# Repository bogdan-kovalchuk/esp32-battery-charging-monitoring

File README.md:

# ESP32 Battery Charging Monitor

An ESP32-based 12 V battery voltage monitor. The firmware measures battery
voltage, while a Flask backend delivers notifications to a Signal group through
`signal-cli`.

```text
ESP32 -- HTTP or HTTPS --> Flask -- SQLite outbox --> signal-cli --> Signal group
```

## Features

- Voltage sampling every 60 seconds
- Immediate `ALERT` when voltage drops to or below the critical threshold
- Immediate `INFO` when voltage recovers
- Separate reminder intervals for INFO and ALERT states
- Fallback WiFi access point with a web configuration form
- CRC-protected ESP32 configuration stored in alternating NVS slots
- Persistent SQLite outbox with retries and `event_id` deduplication
- Optional HTTP or HTTPS transport
- Health check and Prometheus metrics

## Project structure

| Path | Purpose |
|---|---|
| `firmware/` | PlatformIO/Arduino firmware for ESP32 |
| `server/` | Flask API and signal-cli integration |
| `firmware/test/` | Host-side firmware logic tests |
| `server/tests/` | Backend tests |
| `hardware/battery-monitor-rev-a/` | KiCad 10 project of the rev-a PCB and its production package |

## Hardware

### Rev-a PCB

[`hardware/battery-monitor-rev-a/`](hardware/battery-monitor-rev-a/) is a
dedicated board: ESP32-S3-WROOM-1-N16R8, Ra-02 433 MHz LoRa, ADS1115 battery
voltage measurement for 6-24 V systems (48 V by a part swap), switched LED
voltmeter output; 4 layers, 62 x 50 mm, hand assembly.

| Path | Content |
|---|---|
| `hardware/battery-monitor-rev-a/*.kicad_*`, `lib/`, `3dmodels/` | KiCad 10 schematic (5 sheets), board, design rules, project library and 3D models |
| [`production/`](hardware/battery-monitor-rev-a/production/README.md) | Gerber ZIP for a standard JLCPCB 4-layer order, drill, IPC-D-356, BOM, purchase workbook, schematic PDF, assembly drawings, STEP, `manifest.sha256` |
| [`ASSEMBLY-NOTES.md`](hardware/battery-monitor-rev-a/production/03-documentation/ASSEMBLY-NOTES.md) | Pin map, hand-assembly order, firmware obligations, bring-up tests |

The firmware in `firmware/` still targets the ESP32 DevKit prototype below; it
is not yet ported to the ESP32-S3 and the rev-a pin map.

### DevKit prototype

| Signal | ESP32 pin | Notes |
|---|---:|---|
| Voltage divider | GPIO 32 | ADC input, 30 kOhm / 7.5 kOhm |
| Button | GPIO 34 | Requires an external 10 kOhm pull-down |
| Divider/gauge enable | GPIO 4 | Through a transistor and 1 kOhm resistor |

The ADC calibration factor is `CORR_FACTOR` in
`firmware/include/app_config.h`.

## Firmware

Create the configuration file:

```bash
cp firmware/include/secrets.h.example firmware/include/secrets.h
```

Set the WiFi credentials, backend host, API token, and passwords. `secrets.h`
is ignored by Git. Its values provide the initial defaults; after the first
boot, runtime configuration is stored in NVS.

Build and upload:

```bash
pio run -d firmware -e esp32dev
pio run -d firmware -e esp32dev -t upload
pio device monitor -b 115200
```

### HTTP and HTTPS

The configuration template uses HTTP by default:

```cpp
#define SERVER_PORT 5000
#define SERVER_USE_TLS 0
#define SERVER_ROOT_CA ""
```

Existing private `secrets.h` files without the TLS macros also continue to use
HTTP.

To enable HTTPS, select the TLS port and provide the PEM CA root:

```cpp
#define SERVER_PORT 443
#define SERVER_USE_TLS 1
#define SERVER_ROOT_CA \
  "-----BEGIN CERTIFICATE-----\n" \
  "...\n" \
  "-----END CERTIFICATE-----\n"
```

The CA root is required only when HTTPS is enabled.

### Fallback access point

If the ESP32 cannot connect to WiFi within 30 seconds, it starts the configured
fallback access point while continuing STA connection attempts in the
background.

1. Connect to the network configured by `AP_SSID`.
2. Open `http://192.168.4.1/`.
3. Sign in with `WEB_USER` and `WEB_PASSWORD`.
4. Update the WiFi, backend, threshold, and interval settings.
5. Save the configuration.

The fallback access point stops after the STA connection remains stable.
Holding the button for 10 seconds restores the compile-time defaults.

## Backend

The backend requires Python 3.10+ and an installed `signal-cli`. Follow the
official [signal-cli README](https://github.com/AsamK/signal-cli) for current
installation and account setup instructions.

```bash
cd server
python3 -m venv .venv
. .venv/bin/activate
pip install -r requirements.txt
cp .env.example .env
```

Set at least these values:

```dotenv
SIGNAL_USER=+380XXXXXXXXX
SIGNAL_GROUP_ID=group-id
API_TOKEN=same-token-as-in-firmware
```

Start the backend:

```bash
python -m battery_monitor.wsgi
```

Before opening the socket, the backend verifies the signal-cli binary, account,
and target group. Accepted events are persisted in
`server/.data/outbox.sqlite3` and then sent sequentially through signal-cli.

## API

`POST /send` requires `Authorization: Bearer <API_TOKEN>`.

```json
{
  "event_id": "device-boot-sequence",
  "device_id": "BATT#1",
  "msg_type": "ALERT",
  "voltage": 10.8,
  "critical_voltage": 11.0
}
```

| Status | Meaning |
|---:|---|
| `202` | Event persisted or previously accepted |
| `400` | Invalid payload |
| `401` | Invalid API token |
| `413` | Request body too large |
| `503` | Outbox full; retry with the same `event_id` |

Additional endpoints:

- `GET /healthcheck` – public unless `HEALTHCHECK_REQUIRE_AUTH=true`
- `GET /metrics` – requires the bearer token unless `METRICS_REQUIRE_AUTH=false`
- `GET /signal-cli/version` – follows the `/metrics` setting

## Tests

```bash
pio test -d firmware -e native
pio run -d firmware -e esp32dev-ci

cd server
python -m pytest
```

On Windows, `firmware/scripts/native_toolchain.py` lets `pio test -e native`
use the MinGW toolchain bundled with PlatformIO when no `gcc` is on `PATH`.

`esp32dev-ci` uses dummy credentials for compile checks only. Upload firmware
with the `esp32dev` environment and your own `secrets.h`.

## Limitations

- HTTP does not encrypt the API token; enable HTTPS on untrusted networks.
- The ESP32 configuration portal uses HTTP.
- ESP32 NVS is not encrypted.
- Devices using the same `API_TOKEN` share access. Use individual tokens when
  separate device identities are required.

## License

[MIT](LICENSE)

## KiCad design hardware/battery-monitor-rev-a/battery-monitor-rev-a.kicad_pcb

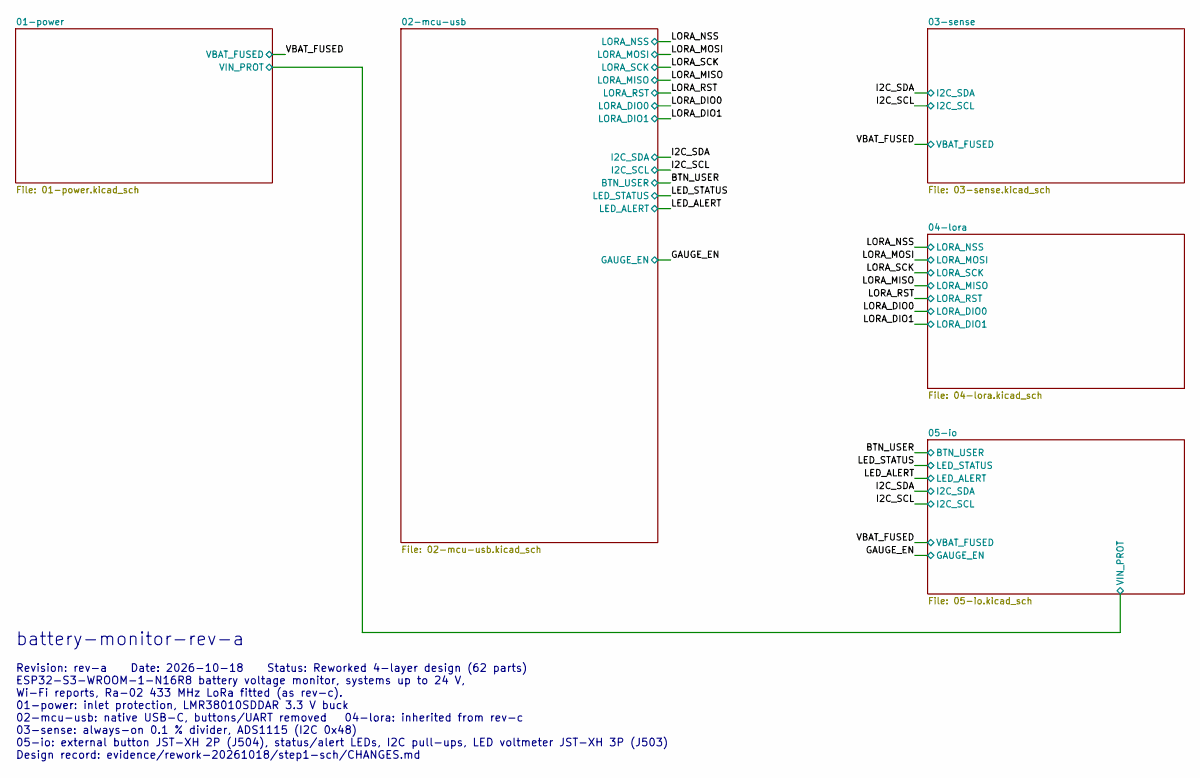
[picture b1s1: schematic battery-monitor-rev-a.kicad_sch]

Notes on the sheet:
battery-monitor-rev-a
Revision: rev-a Date: 2026-10-18 Status: Reworked 4-layer design (62 parts) ESP32-S3-WROOM-1-N16R8 battery voltage monitor, systems up to 24 V, Wi-Fi reports, Ra-02 433 MHz LoRa fitted (as rev-c). 01-power: inlet protection, LMR38010SDDAR 3.3 V buck 02-mcu-usb: native USB-C, buttons/UART removed 04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

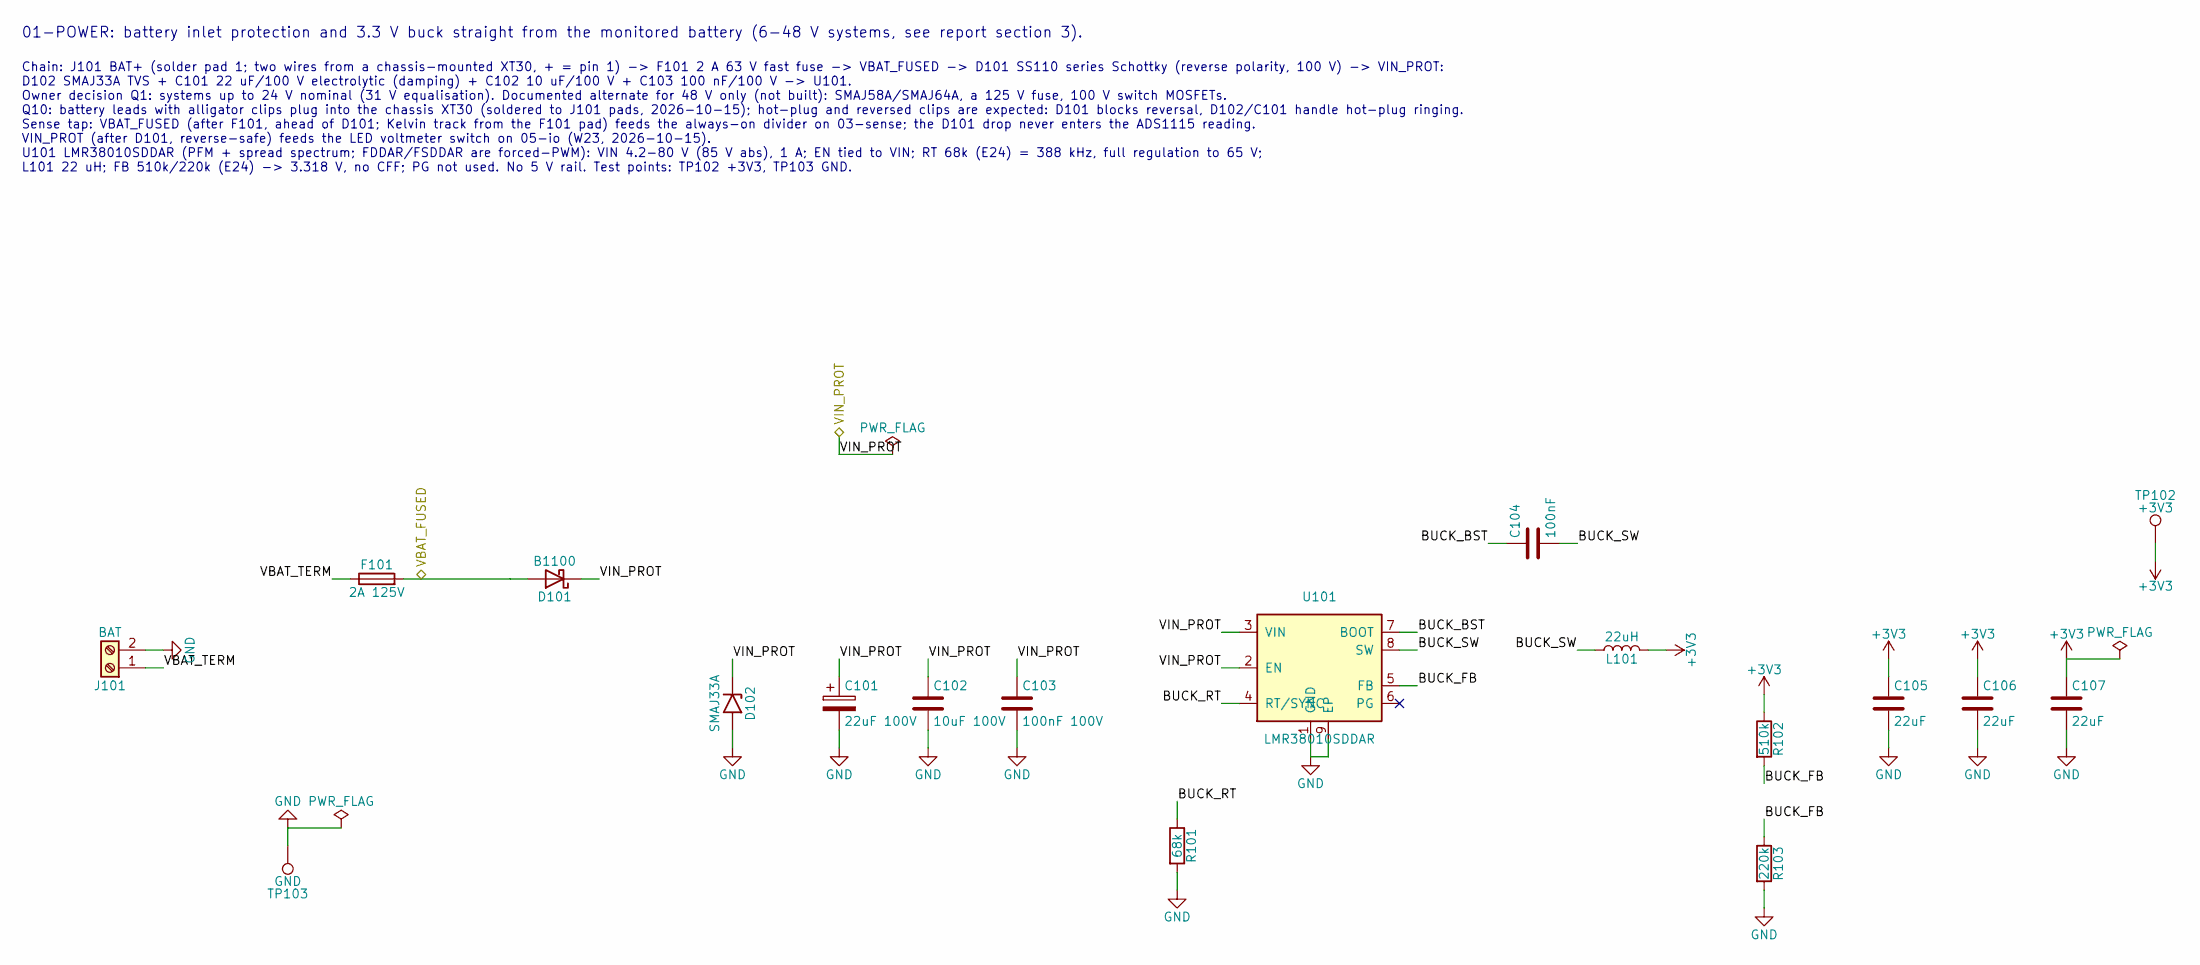
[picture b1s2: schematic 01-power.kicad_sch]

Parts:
C101: 22uF 100V; CP_Elec_8x10; MPN EEE-FK2A220P
C102: 10uF 100V; C_1210_3225Metric; MPN GRM32EC72A106KE05L
C103: 100nF 100V; C_0603_1608Metric; MPN CL10B104KC8NNNC
C104: 100nF; C_0603_1608Metric; MPN CL10B104KB8NNNC
C105, C106, C107: 22uF; C_0805_2012Metric; MPN GRM21BR61E226ME44L
D101: B1100; D_SMA; MPN B1100-13-F
D102: SMAJ33A; D_SMA; MPN SMAJ33A-TR
F101: 2A 125V; Fuse_Littelfuse-NANO2-451_453; MPN 0451002.MRL
J101: BAT; SolderWire-0.75sqmm_1x02_P4.8mm_D1.25mm_OD2.3mm
L101: 22uH; L_Bourns_SRN6045TA; MPN SRN6045-220M
R101: 68k; R_0603_1608Metric; MPN RC0603FR-0768KL
R102: 510k; R_0603_1608Metric; MPN 0603SAF5103T5E
R103: 220k; R_0603_1608Metric; MPN RC0603FR-07220KL
TP102: +3V3; TestPoint_Pad_D1.5mm
TP103: GND; TestPoint_Pad_D1.5mm
U101: LMR38010SDDAR; TI_SO-PowerPAD-8; MPN LMR38010SDDAR

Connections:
+3V3: C105.1, C106.1, C107.1, L101.2, R102.1, TP102.1; also elsewhere on the board
/01-power/BUCK_BST: C104.1, U101.7 (BOOT)
/01-power/BUCK_FB: R102.2, R103.1, U101.5 (FB)
/01-power/BUCK_RT: R101.1, U101.4 (RT/SYNC)
/01-power/BUCK_SW: C104.2, L101.1, U101.8 (SW)
/01-power/VBAT_TERM: F101.1, J101.1
/01-power/VIN_PROT: C101.1, C102.1, C103.1, D101.1 (K), D102.1 (A1), U101.2 (EN), U101.3 (VIN); also elsewhere on the board
/VBAT_FUSED: D101.2 (A), F101.2; also elsewhere on the board
GND: C101.2, C102.2, C103.2, C105.2, C106.2, C107.2, D102.2 (A2), J101.2, R101.2, R103.2, TP103.1, U101.1 (GND), U101.9 (EP); also elsewhere on the board

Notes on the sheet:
01-POWER: battery inlet protection and 3.3 V buck straight from the monitored battery (6-48 V systems, see report section 3).
Chain: J101 BAT+ (solder pad 1; two wires from a chassis-mounted XT30, + = pin 1) -> F101 2 A 63 V fast fuse -> VBAT_FUSED -> D101 SS110 series Schottky (reverse polarity, 100 V) -> VIN_PROT: D102 SMAJ33A TVS + C101 22 uF/100 V electrolytic (damping) + C102 10 uF/100 V + C103 100 nF/100 V -> U101. 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

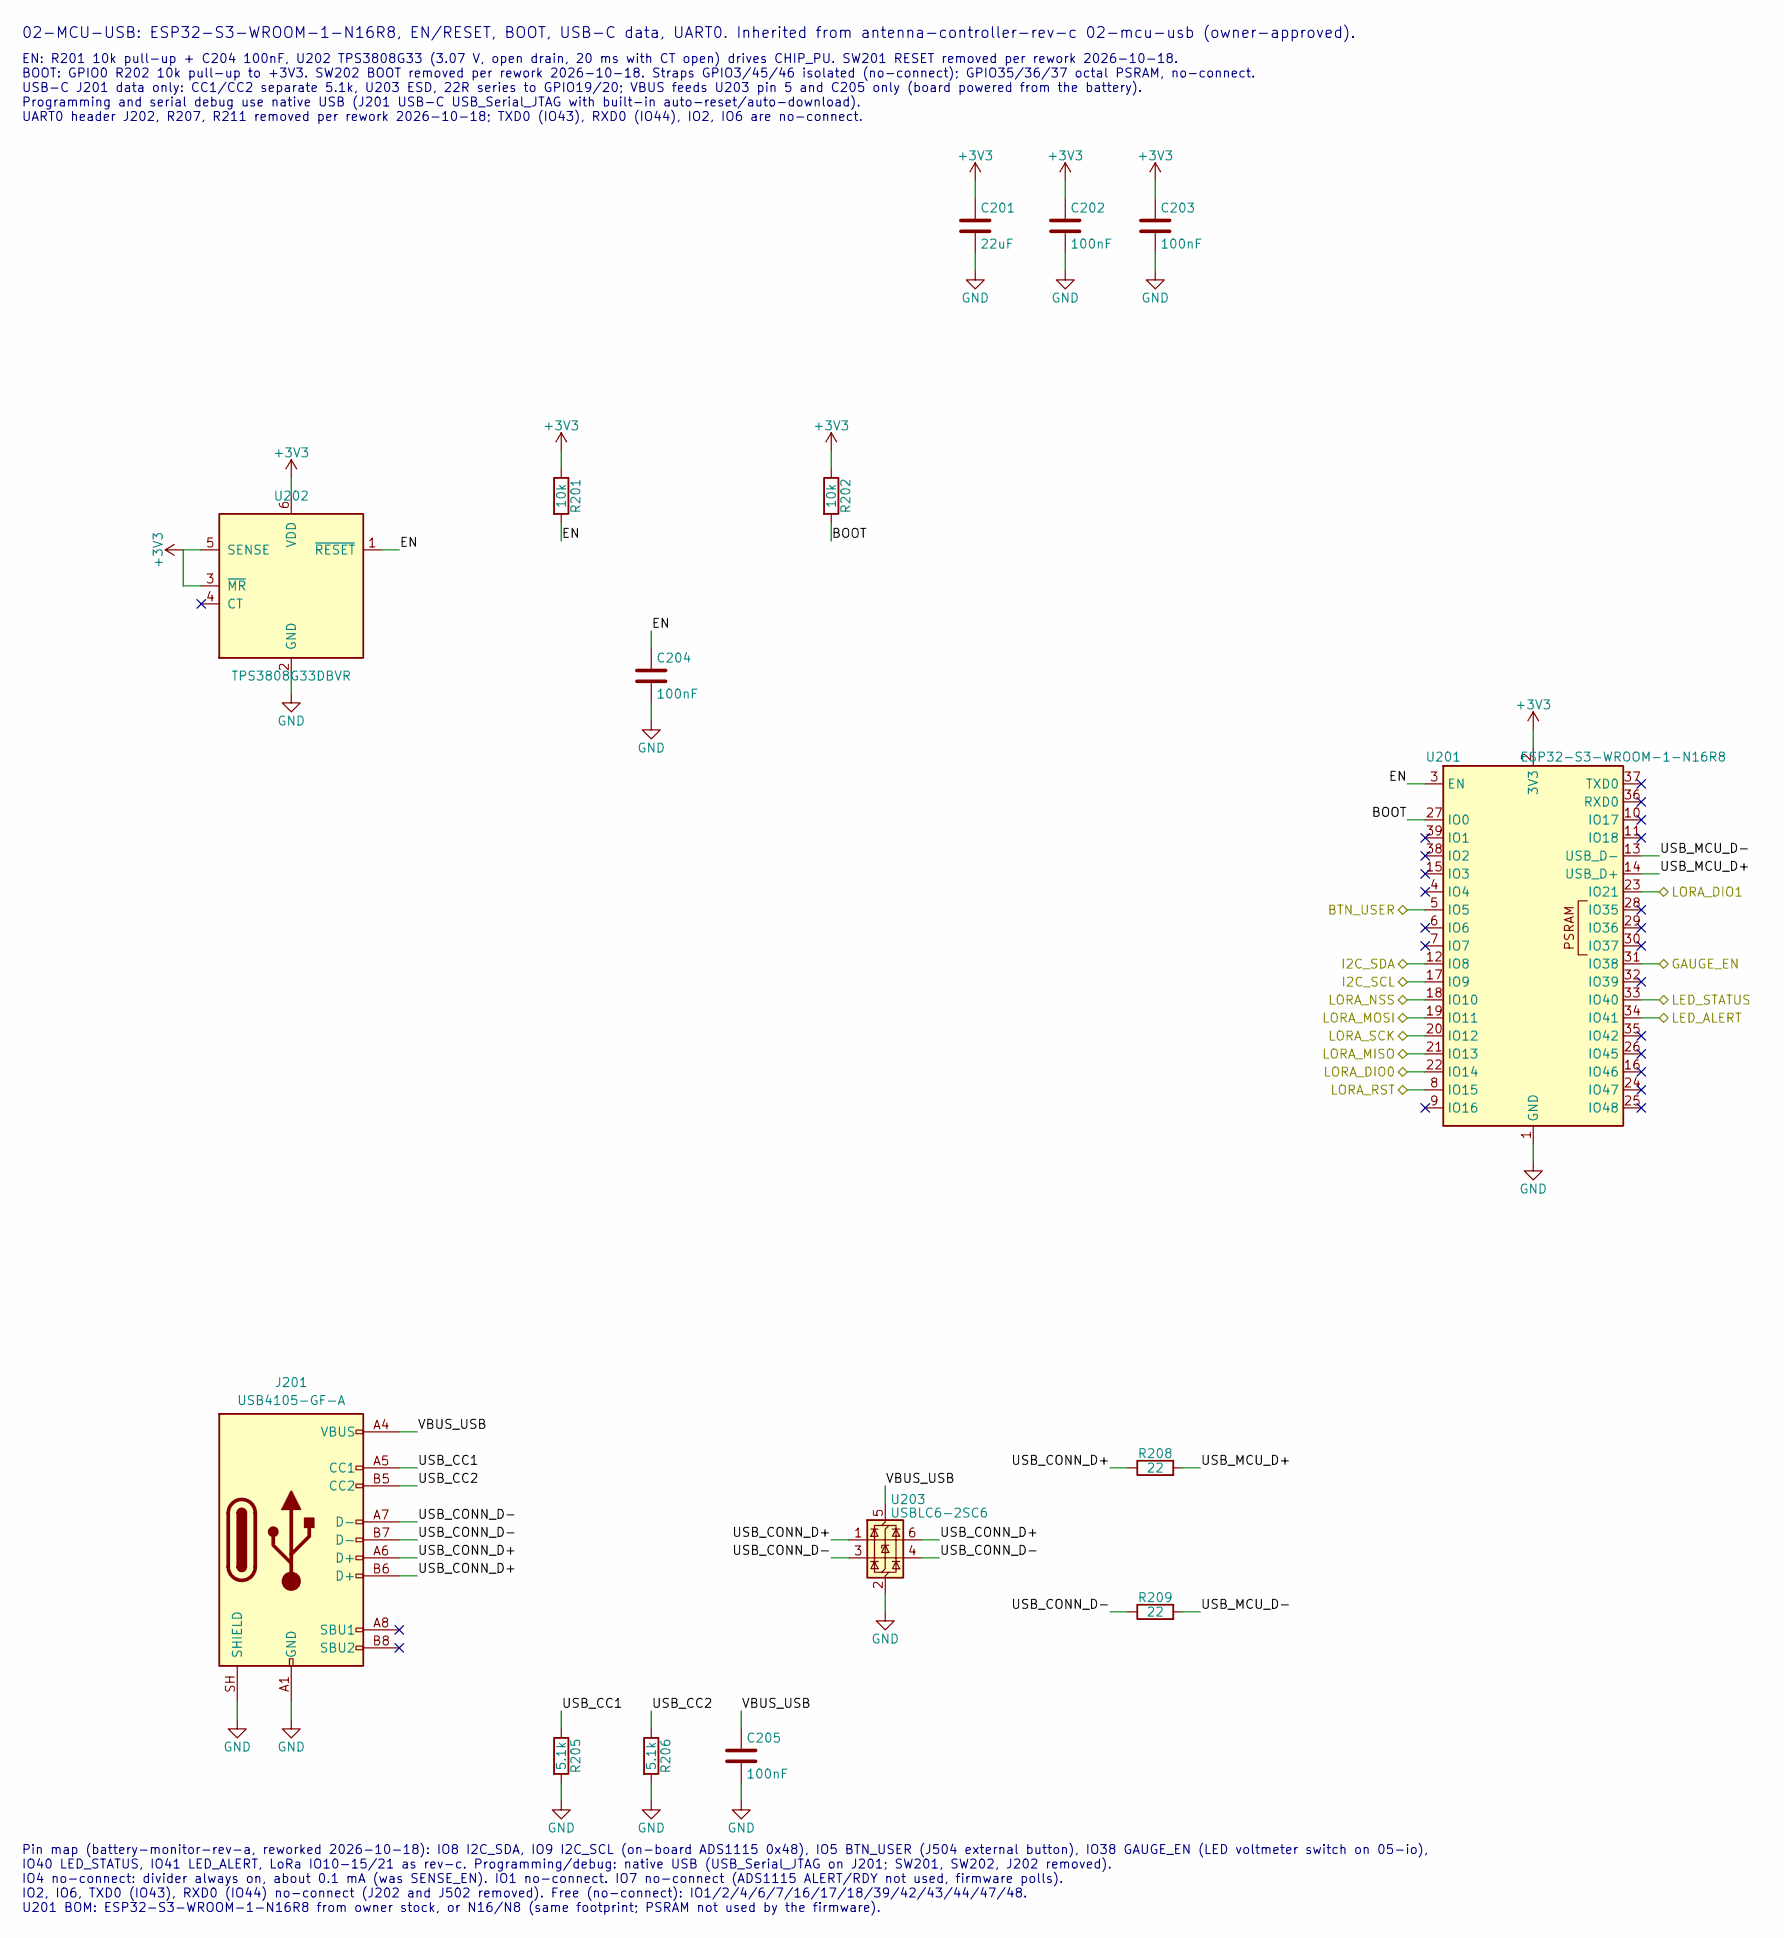
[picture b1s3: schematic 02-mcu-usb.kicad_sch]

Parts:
C201: 22uF; C_0805_2012Metric; MPN GRM21BR61E226ME44L
C202, C203, C204, C205: 100nF; C_0603_1608Metric; MPN CL10B104KB8NNNC
J201: USB4105-GF-A; USB_C_Receptacle_HRO_TYPE-C-31-M-12; MPN USB4105-GF-A
R201, R202: 10k; R_0603_1608Metric; MPN 0603SAF1002T5E
R205, R206: 5.1k; R_0603_1608Metric; MPN RC0603FR-075K1L
R208, R209: 22; R_0603_1608Metric; MPN RC0603FR-0722RL
U201: ESP32-S3-WROOM-1-N16R8; ESP32-S3-WROOM-1; MPN ESP32-S3-WROOM-1-N16R8 (or -N16 / -N8, 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
U202: TPS3808G33DBVR; SOT-23-6; MPN TPS3808G33DBVR
U203: USBLC6-2SC6; SOT-23-6; MPN USBLC6-2SC6

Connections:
+3V3: C201.1, C202.1, C203.1, R201.1, R202.1, U201.2 (3V3), U202.3 (~MR), U202.5 (SENSE), U202.6 (VDD); also elsewhere on the board
/02-mcu-usb/BOOT: R202.2, U201.27 (IO0)
/02-mcu-usb/EN: C204.1, R201.2, U201.3 (EN), U202.1 (~RESET)
/02-mcu-usb/USB_CC1: J201.A5 (CC1), R205.1
/02-mcu-usb/USB_CC2: J201.B5 (CC2), R206.1
/02-mcu-usb/USB_CONN_D+: J201.A6 (D+), J201.B6 (D+), R208.1, U203.1 (I/O1), U203.6 (I/O1)
/02-mcu-usb/USB_CONN_D-: J201.A7 (D-), J201.B7 (D-), R209.1, U203.3 (I/O2), U203.4 (I/O2)
/02-mcu-usb/USB_MCU_D+: R208.2, U201.14 (USB_D+)
/02-mcu-usb/USB_MCU_D-: R209.2, U201.13 (USB_D-)
/02-mcu-usb/VBUS_USB: C205.1, J201.A4 (VBUS), J201.A9 (VBUS), J201.B4 (VBUS), J201.B9 (VBUS), U203.5 (VBUS)
/BTN_USER: U201.5 (IO5); also elsewhere on the board
/GAUGE_EN: U201.31 (IO38); also elsewhere on the board
/I2C_SCL: U201.17 (IO9); also elsewhere on the board
/I2C_SDA: U201.12 (IO8); also elsewhere on the board
/LED_ALERT: U201.34 (IO41); also elsewhere on the board
/LED_STATUS: U201.33 (IO40); also elsewhere on the board
/LORA_DIO0: U201.22 (IO14); also elsewhere on the board
/LORA_DIO1: U201.23 (IO21); also elsewhere on the board
/LORA_MISO: U201.21 (IO13); also elsewhere on the board
/LORA_MOSI: U201.19 (IO11); also elsewhere on the board
/LORA_NSS: U201.18 (IO10); also elsewhere on the board
/LORA_RST: U201.8 (IO15); also elsewhere on the board
/LORA_SCK: U201.20 (IO12); also elsewhere on the board
GND: C201.2, C202.2, C203.2, C204.2, C205.2, J201.A1 (GND), J201.A12 (GND), J201.B1 (GND), J201.B12 (GND), J201.SH (SHIELD), R205.2, R206.2, U201.1 (GND), U201.40 (GND), U201.41 (GND), U202.2 (GND), U203.2 (GND); also elsewhere on the board

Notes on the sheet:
02-MCU-USB: ESP32-S3-WROOM-1-N16R8, EN/RESET, BOOT, USB-C data, UART0. Inherited from antenna-controller-rev-c 02-mcu-usb (owner-approved).
EN: R201 10k pull-up + C204 100nF, U202 TPS3808G33 (3.07 V, open drain, 20 ms with CT open) drives CHIP_PU. SW201 RESET removed per rework 2026-10-18. BOOT: GPIO0 R202 10k pull-up to +3V3. SW202 BOOT removed per rework 2026-10-18. Straps GPIO3/45/46 isolated (no-connect); GPIO35/36/37 octal PSRAM, 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
Pin map (battery-monitor-rev-a, reworked 2026-10-18): IO8 I2C_SDA, IO9 I2C_SCL (on-board ADS1115 0x48), IO5 BTN_USER (J504 external button), IO38 GAUGE_EN (LED voltmeter switch on 05-io), IO40 LED_STATUS, IO41 LED_ALERT, LoRa IO10-15/21 as rev-c. Programming/debug: native USB (USB_Serial_JTAG on J2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

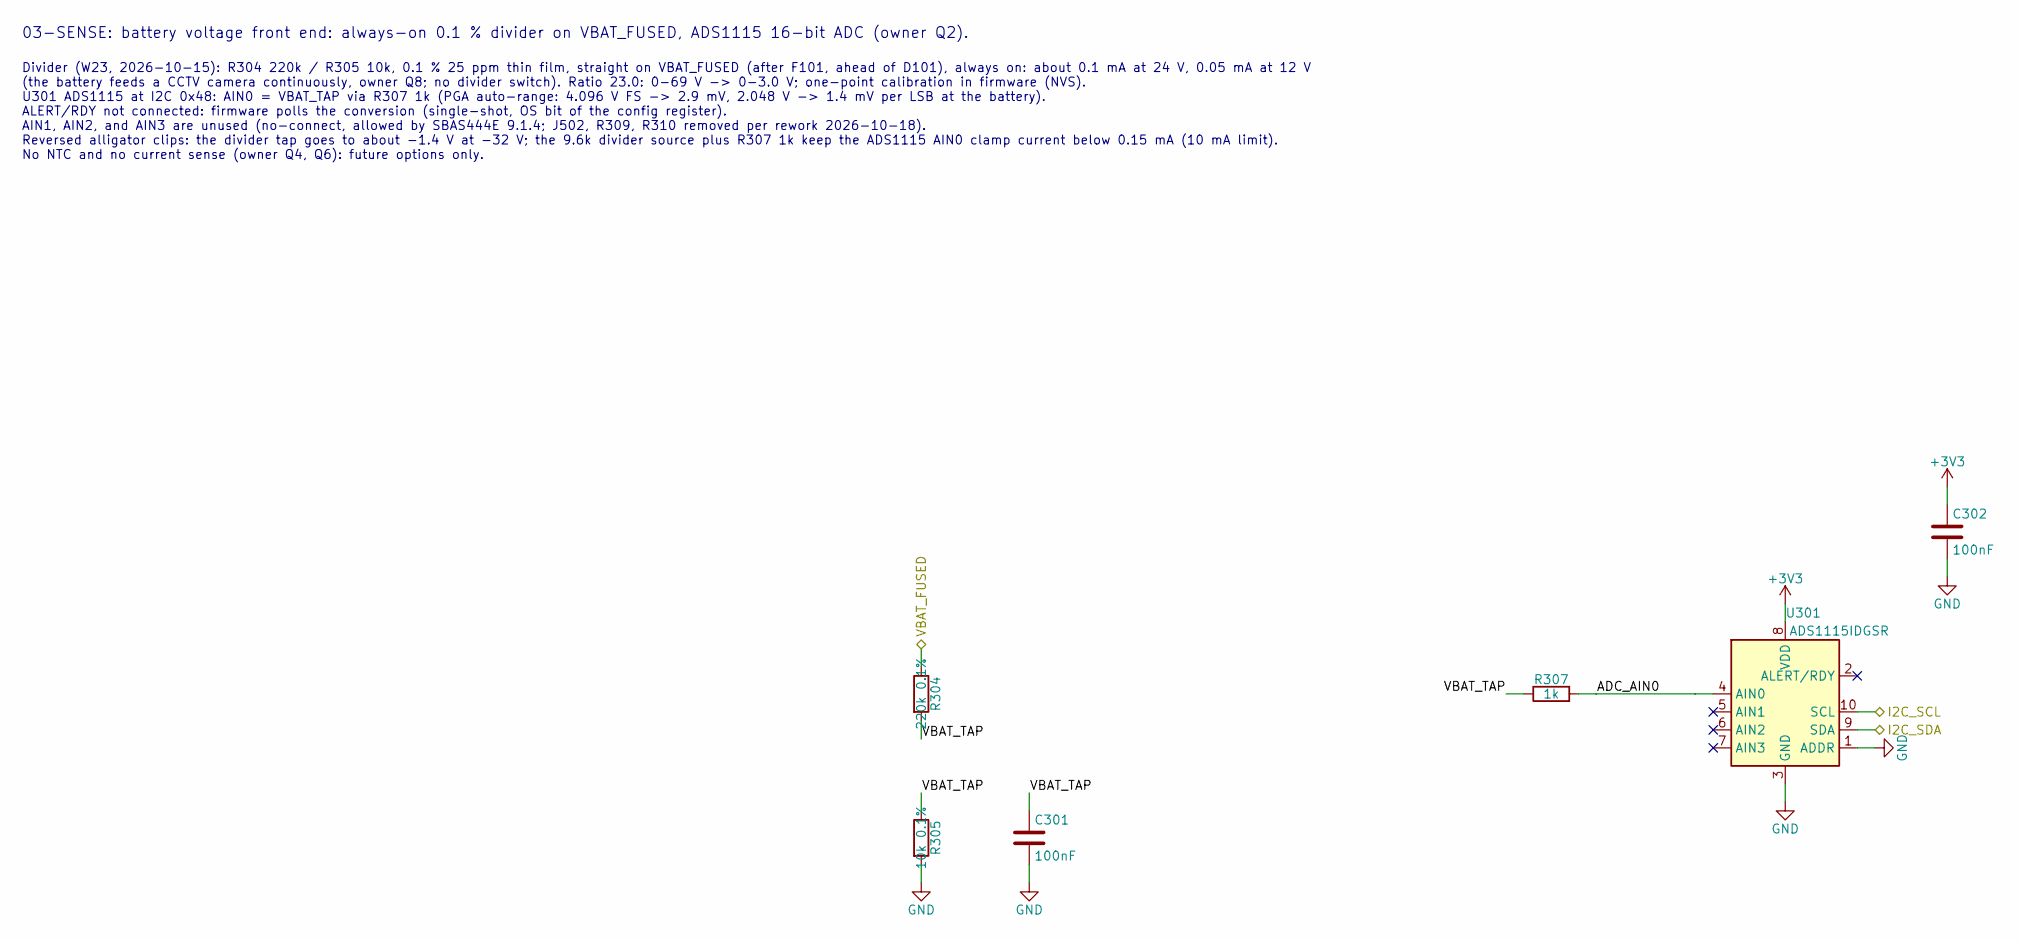
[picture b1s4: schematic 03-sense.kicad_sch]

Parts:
C301, C302: 100nF; C_0603_1608Metric; MPN CL10B104KB8NNNC
R304: 220k 0.1%; R_0805_2012Metric; MPN ERA-6AEB224V
R305: 10k 0.1%; R_0603_1608Metric; MPN RT0603BRD0710KL
R307: 1k; R_0603_1608Metric; MPN RC0603FR-071KL
U301: ADS1115IDGSR; TSSOP-10_3x3mm_P0.5mm; MPN ADS1115IDGSR

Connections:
+3V3: C302.1, U301.8 (VDD); also elsewhere on the board
/03-sense/ADC_AIN0: R307.2, U301.4 (AIN0)
/03-sense/VBAT_TAP: C301.1, R304.2, R305.1, R307.1
/I2C_SCL: U301.10 (SCL); also elsewhere on the board
/I2C_SDA: U301.9 (SDA); also elsewhere on the board
/VBAT_FUSED: R304.1; also elsewhere on the board
GND: C301.2, C302.2, R305.2, U301.1 (ADDR), U301.3 (GND); also elsewhere on the board

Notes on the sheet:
03-SENSE: battery voltage front end: always-on 0.1 % divider on VBAT_FUSED, ADS1115 16-bit ADC (owner Q2).
Divider (W23, 2026-10-15): R304 220k / R305 10k, 0.1 % 25 ppm thin film, straight on VBAT_FUSED (after F101, ahead of D101), always on: about 0.1 mA at 24 V, 0.05 mA at 12 V (the battery feeds a CCTV camera continuously, owner Q8; no divider switch). Ratio 23.0: 0-69 V -> 0-3.0 V; one-point calibra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

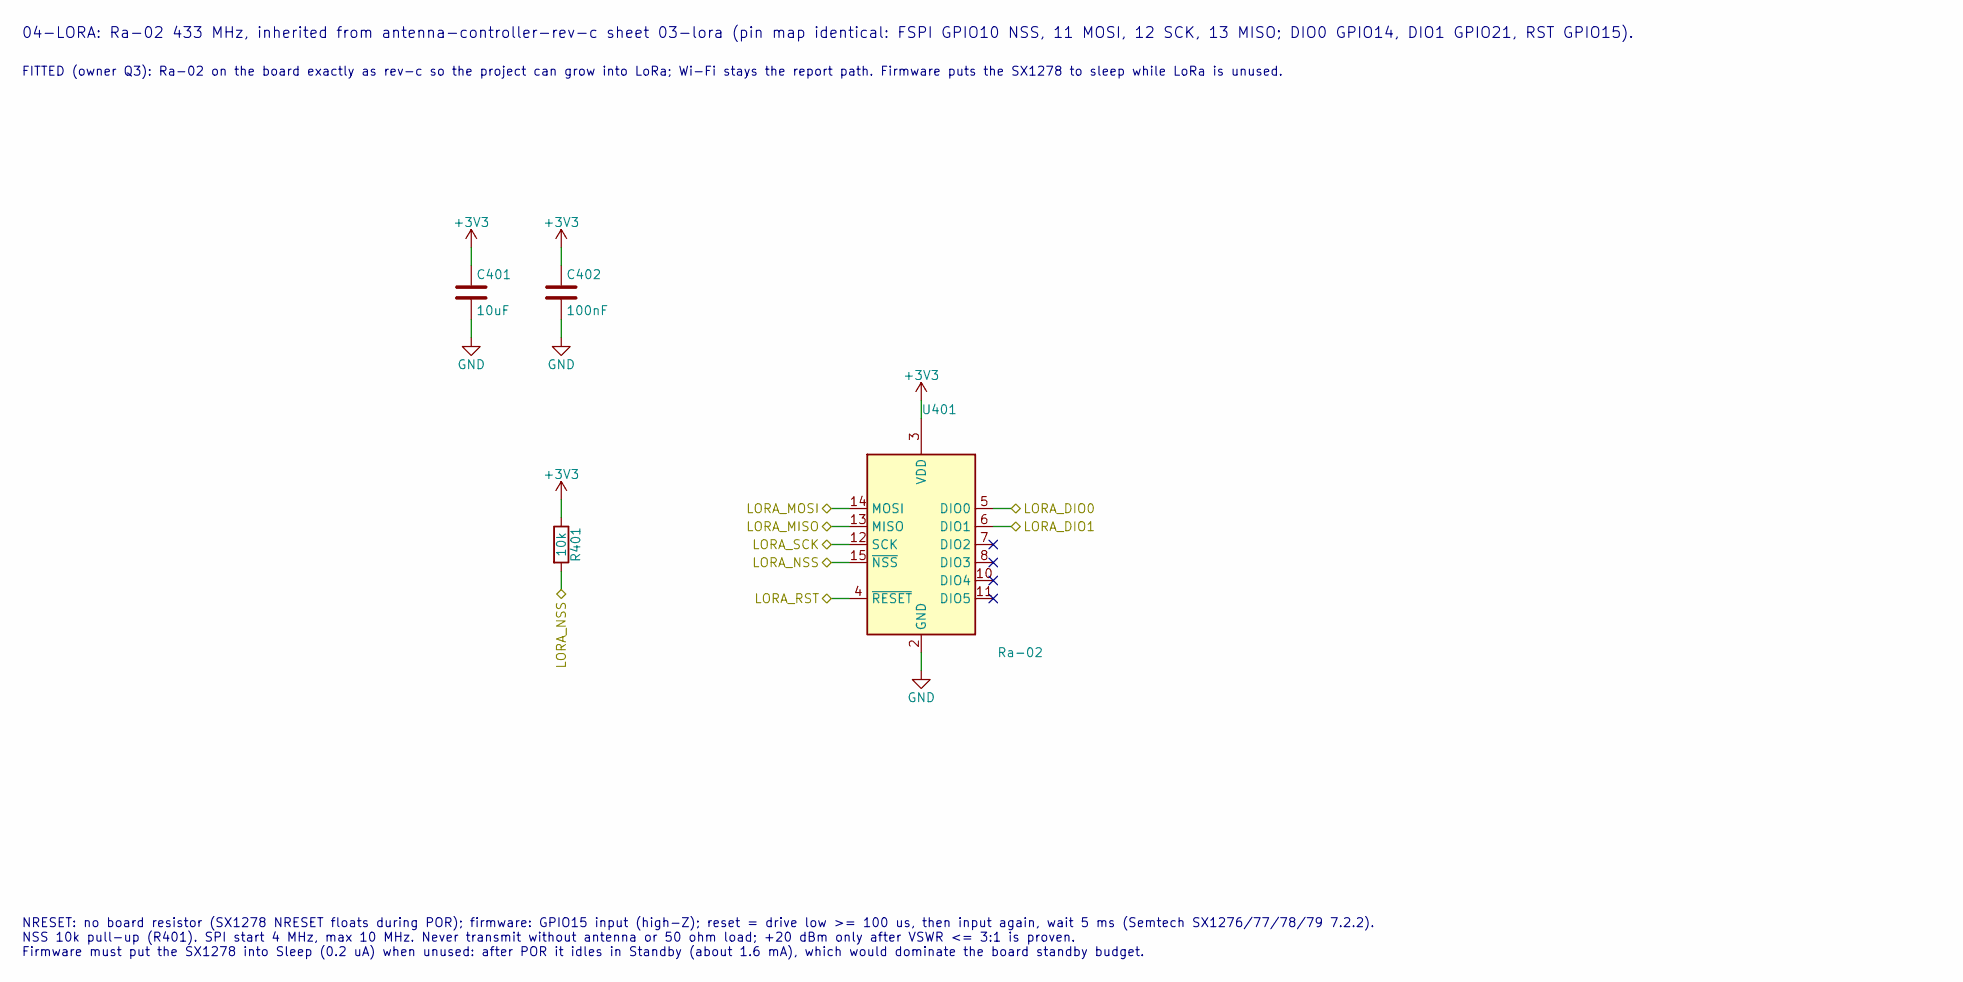
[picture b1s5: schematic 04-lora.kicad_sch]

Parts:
C401: 10uF; C_0805_2012Metric; MPN CL21A106KAYNNNE
C402: 100nF; C_0603_1608Metric; MPN CL10B104KB8NNNC
R401: 10k; R_0603_1608Metric; MPN 0603SAF1002T5E
U401: Ra-02; Ra02_Source; MPN Ra-02

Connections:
+3V3: C401.1, C402.1, R401.1, U401.3 (VDD); also elsewhere on the board
/LORA_DIO0: U401.5 (DIO0); also elsewhere on the board
/LORA_DIO1: U401.6 (DIO1); also elsewhere on the board
/LORA_MISO: U401.13 (MISO); also elsewhere on the board
/LORA_MOSI: U401.14 (MOSI); also elsewhere on the board
/LORA_NSS: R401.2, U401.15 (~NSS); also elsewhere on the board
/LORA_RST: U401.4 (~RESET); also elsewhere on the board
/LORA_SCK: U401.12 (SCK); also elsewhere on the board
GND: C401.2, C402.2, U401.1 (GND), U401.2 (GND), U401.9 (GND), U401.16 (GND); also elsewhere on the board

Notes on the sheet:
04-LORA: Ra-02 433 MHz, inherited from antenna-controller-rev-c sheet 03-lora (pin map identical: FSPI GPIO10 NSS, 11 MOSI, 12 SCK, 13 MISO; DIO0 GPIO14, DIO1 GPIO21, RST GPIO15).
FITTED (owner Q3): Ra-02 on the board exactly as rev-c so the project can grow into LoRa; Wi-Fi stays the report path. Firmware puts the SX1278 to sleep while LoRa is unused.
NRESET: no board resistor (SX1278 NRESET floats during POR); firmware: GPIO15 input (high-Z); reset = drive low >= 100 us, then input again, wait 5 ms (Semtech SX1276/77/78/79 7.2.2). NSS 10k pull-up (R401). SPI start 4 MHz, max 10 MHz. Never transmit without antenna or 50 ohm load; +20 dBm only af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

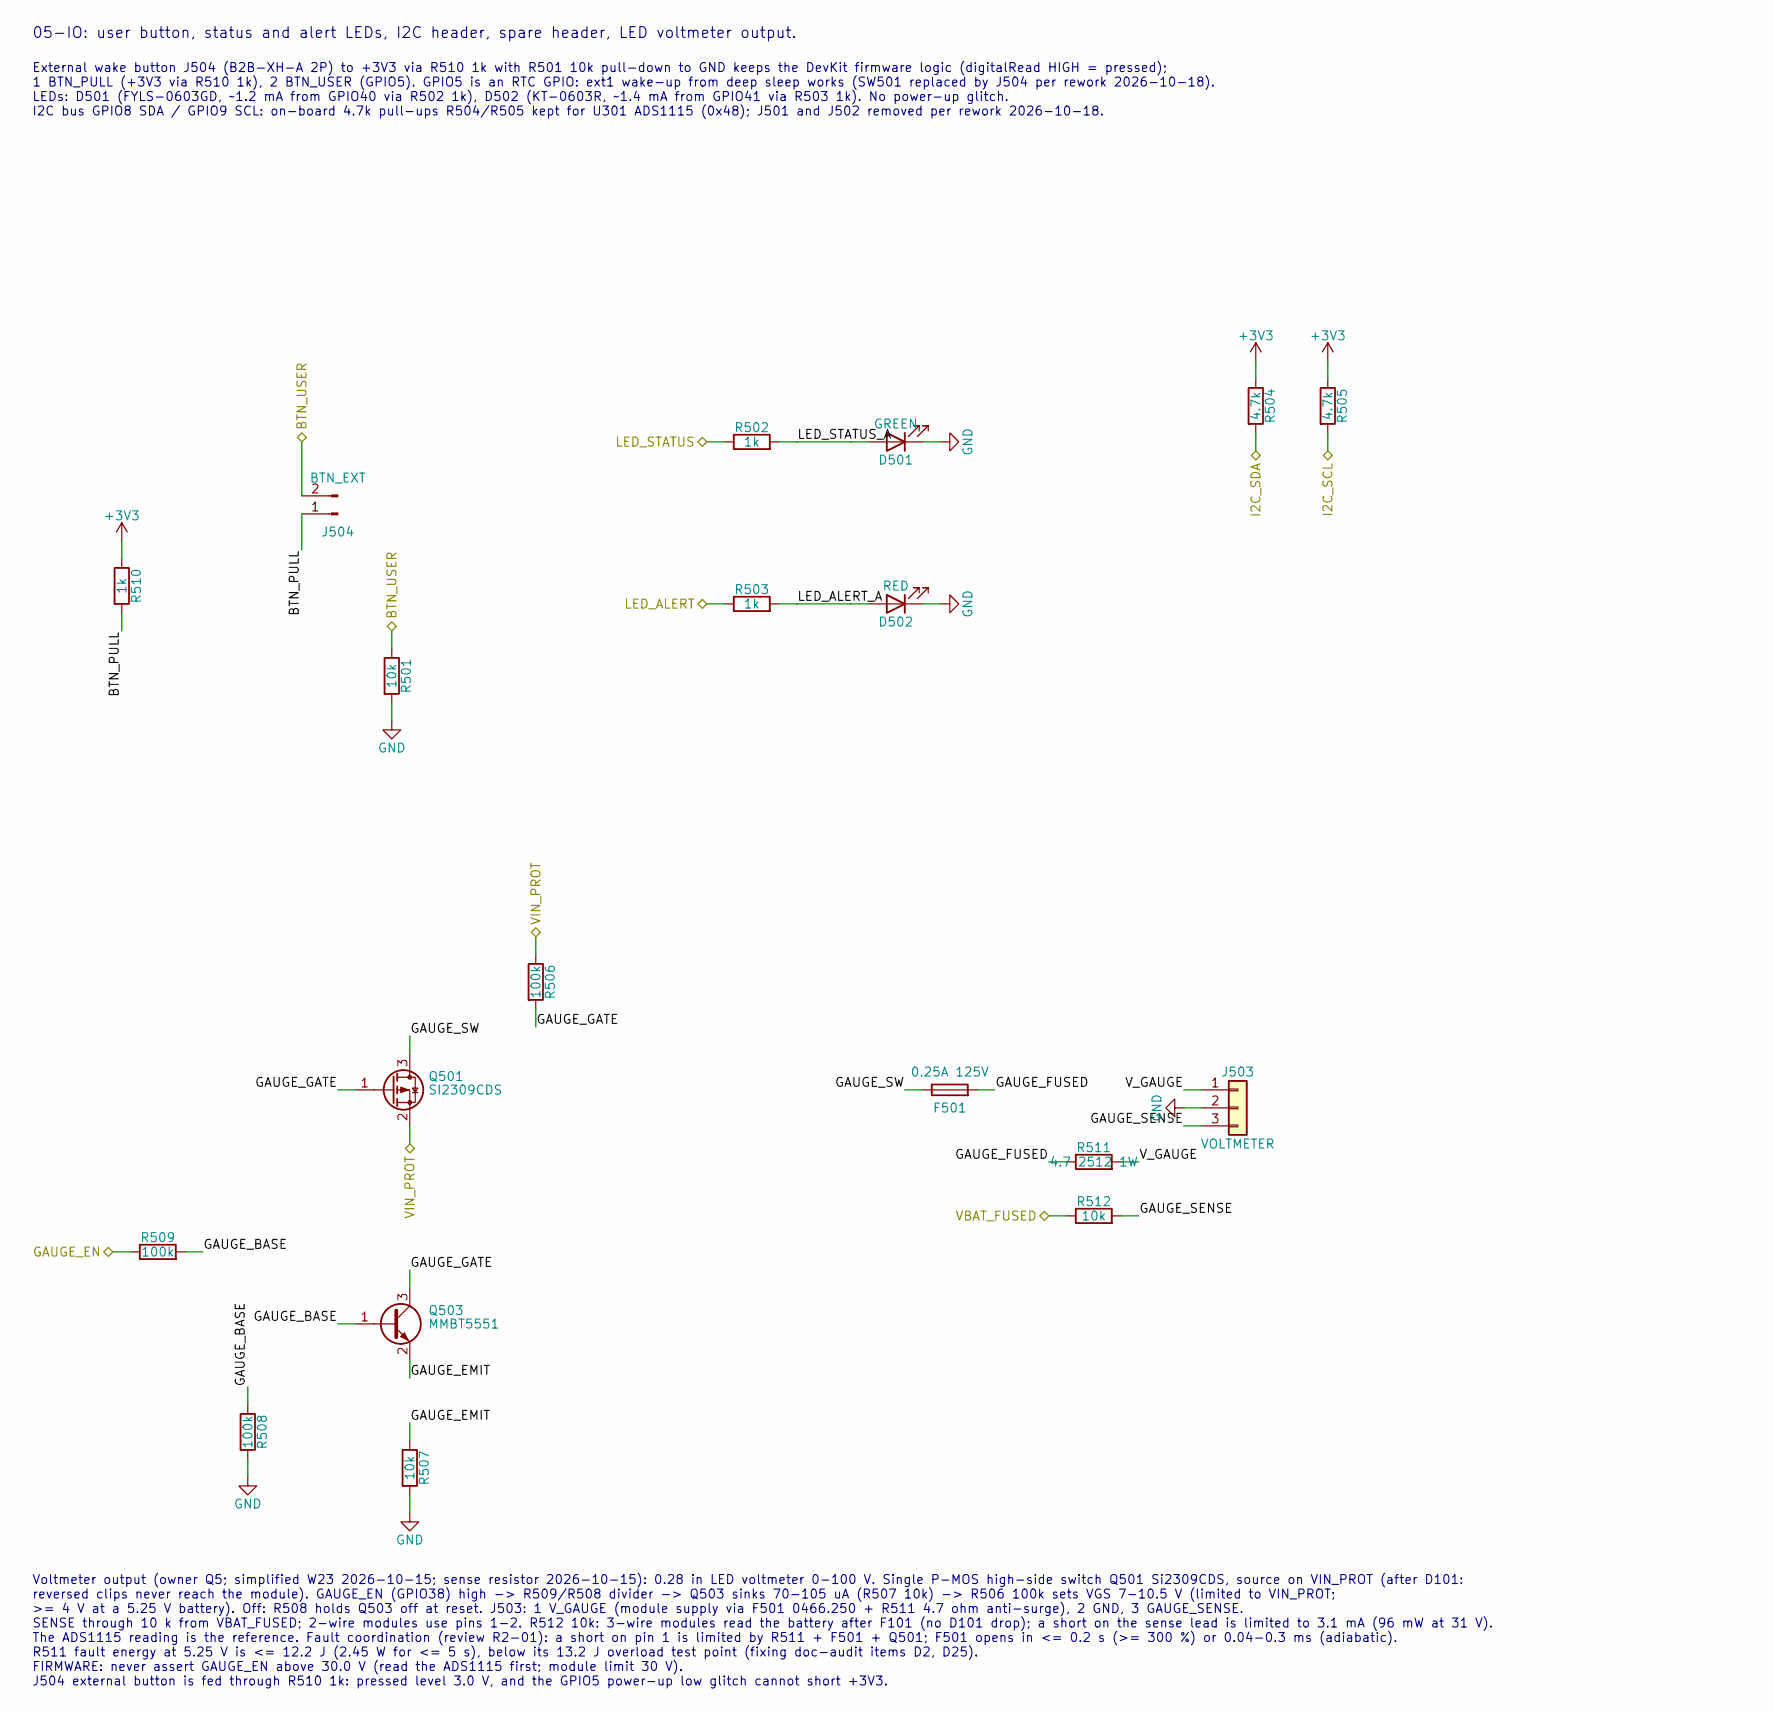
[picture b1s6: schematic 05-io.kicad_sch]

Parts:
D501: GREEN; LED_0603_1608Metric; MPN LTST-C191KGKT
D502: RED; LED_0603_1608Metric; MPN KP-1608SURCK
F501: 0.25A 125V; Fuse_1206_3216Metric; MPN 0466.250NRHF
J503: VOLTMETER; JST_XH_B3B-XH-A_1x03_P2.50mm_Vertical; MPN B3B-XH-A(LF)(SN)
J504: BTN_EXT; JST_XH_B2B-XH-A_1x02_P2.50mm_Vertical; MPN B2B-XH-A(LF)(SN)
Q501: SI2309CDS; SOT-23; MPN SI2309CDS-T1-GE3
Q503: MMBT5551; SOT-23; MPN MMBT5551LT1G
R501, R507: 10k; R_0603_1608Metric; MPN 0603SAF1002T5E
R502, R503, R510: 1k; R_0603_1608Metric; MPN RC0603FR-071KL
R504, R505: 4.7k; R_0603_1608Metric; MPN 0603SAF4701T5E
R506, R508, R509: 100k; R_0603_1608Metric; MPN AC0603FR-07100KL
R511: 4.7 2512 1W; R_2512_6332Metric; MPN RC2512JK-074R7L
R512: 10k; R_1206_3216Metric; MPN 1206S4F1002T5E

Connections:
+3V3: R504.1, R505.1, R510.1; also elsewhere on the board
/01-power/VIN_PROT: Q501.2 (S), R506.1; also elsewhere on the board
/05-io/BTN_PULL: J504.1, R510.2
/05-io/GAUGE_BASE: Q503.1 (B), R508.1, R509.2
/05-io/GAUGE_EMIT: Q503.2 (E), R507.1
/05-io/GAUGE_FUSED: F501.2, R511.1
/05-io/GAUGE_GATE: Q501.1 (G), Q503.3 (C), R506.2
/05-io/GAUGE_SENSE: J503.3, R512.2
/05-io/GAUGE_SW: F501.1, Q501.3 (D)
/05-io/LED_ALERT_A: D502.2 (A), R503.2
/05-io/LED_STATUS_A: D501.2 (A), R502.2
/05-io/V_GAUGE: J503.1, R511.2
/BTN_USER: J504.2, R501.1; also elsewhere on the board
/GAUGE_EN: R509.1; also elsewhere on the board
/I2C_SCL: R505.2; also elsewhere on the board
/I2C_SDA: R504.2; also elsewhere on the board
/LED_ALERT: R503.1; also elsewhere on the board
/LED_STATUS: R502.1; also elsewhere on the board
/VBAT_FUSED: R512.1; also elsewhere on the board
GND: D501.1 (K), D502.1 (K), J503.2, R501.2, R507.2, R508.2; also elsewhere on the board

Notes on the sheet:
05-IO: user button, status and alert LEDs, I2C header, spare header, LED voltmeter output.
External wake button J504 (B2B-XH-A 2P) to +3V3 via R510 1k with R501 10k pull-down to GND keeps the DevKit firmware logic (digitalRead HIGH = pressed); 1 BTN_PULL (+3V3 via R510 1k), 2 BTN_USER (GPIO5). GPIO5 is an RTC GPIO: ext1 wake-up from deep sleep works (SW501 replaced by J504 per rework 202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
Voltmeter output (owner Q5; simplified W23 2026-10-15; sense resistor 2026-10-15): 0.28 in LED voltmeter 0-100 V. Single P-MOS high-side switch Q501 Si2309CDS, source on VIN_PROT (after D101: reversed clips never reach the module). GAUGE_EN (GPIO38) high -> R509/R508 divider -> Q503 sinks 70-105 uA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
